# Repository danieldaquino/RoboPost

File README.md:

## An autonomous delivery system — By Daniel D'Aquino and Tim Yue

The aim of this project is to build a line following robot that will follow a line at a constant speed and be able to recognize different docking zones scattered around the track and park there.

**Note:** This project is retired and not under current development. Feel free to contact us if needed.

# SHOW ME THE DEMO!!

Here you go: [RoboPost Demo Video – Youtube](https://www.youtube.com/watch?v=mAnifTH91ZA)

# How does it work?

If you want to know how it works in more details, please visit our wiki!

[How it works — Wiki](https://github.com/danielwalnut/RoboPost/wiki)

# Setting up your own RoboPost

## Getting the hardware

Our custom hardware was designed and built with 3d printed parts, and our own lab-etched PCB boards.
We also made the assembly in a lab.

If you are interested in building your own custom robot based on our design, read on.

### Components needed

1. MSP4305529LP Evaluation Board
2. Particle Photon
3. TI DRV8871 Adafruit Breakout Board
4. 2 6V DC Motors with attached encoder
5. SparkFun Line Follower Sensor Array
6. Grove I2C Color Sensor Module
7. 3d-printed Chassis *(Custom-built)*
8. 3d-printed Motor couple *(Custom-built)*
9. PCB Main Dedicated Board *(Custom-built)*
10. Two wheels
11. Omni-wheel
12. 2 Cell (7.4V) Lipo battery
13. 5V Voltage regulator
14. 3v3 Voltage Regulator
15. Battery Voltage monitor
16. Track *(Custom-built)*
17. Docking Stations *(Custom-built)*

### Schematic

The schematic below is from the PCB Main dedicated board design. It does not include some connections external to the board.

Connections external to the board are done by connecting external pins. This includes:

1. From battery to Battery terminal
2. From motor driver output to motor
3. From power pins (3v3/5v) to sensor power inputs
4. From i2c pins in sensors to i2c bus on the board.

### Installing Software into your computer

Now that you have the hardware, it is time to setup the software!

**Note:** This installation procedure assumes you have a UNIX operating system, such as macOS or Linux, and that you are familiar with the command line. If you are using Microsoft Windows, some steps might be different.
**Note:** This installation procesure also assumes that the RoboPost firmware for both MSP430 and Particle Photon are already flashed into the robot.

1. Remove the robot from packaging.
2. Attach the battery to the velcro tape mount.
3. Connect Voltage Monitor. A loud beep will occur and the voltages should appear on screen.
4. You should see 6.7V minimum on the total voltage monitor. If it is below, it is necessary to charge the battery, or the robot will not work as expected
5. Connect the battery terminals to the Robot.
6. You should immediately see the Line Follower Array and the Photon light up.
7. Setup the Photon to connect to the Wi-Fi network of your choice. *More instructions on that can be found on [https://setup.particle.io](https://setup.particle.io)*
8. Make sure you have Git [https://git-scm.com/](https://git-scm.com/)
9. Clone this repo into your computer
	```$ git clone https://github.com/danielwalnut/RoboPost.git```
10. Generate a keys.json file within the Web folder. This allows the Node.js Application to connect to the correct device.
	```
	$ cd RoboPost/Web
	$ touch keys.json
	```
	Then open the file, and create its contents, **in the following format:**
	```
	{
	    "ID": <YOUR PARTICLE-ACCOUNT-ID IN DOUBLE QUOTES>,
	    "Token": <YOUR PHOTON-ACCESS-KEY IN DOUBLE QUOTES>
	}
	```
	Your keys can be found at [https://console.particle.io](https://console.particle.io)
11. Make sure you have Node.js 8.x.x [https://nodejs.org/en/](https://nodejs.org/en/) and NPM [https://npmjs.com/](https://npmjs.com/)
12. In order to install the required module packages, open a UNIX terminal, make sure you are in the ```Web``` folder and type:
	```$ npm install```
13. Now the installation should have been successful. Make sure the installation happened with no error
14. The software is now setup.

### Operating the Robot

1. After the robot is assembled and software is installed, power the robot by plugging the battery connector with power on the board.
2. Make sure Photon is connected to the same Wi-Fi network as the computer.
3. On a UNIX terminal, go to the ```Web``` folder and start the server:
	```
	$ cd <path-to-RoboPost>/Web
	$ npm start
	```
4. After a few seconds, you should see on the screen

5. Open your favorite web browser and go to [http://localhost:3000/](http://localhost:3000/)
6. The user interface will be displayed, to adjust parameters, click the cog at top right corner and drag the sliders. To set the robot in motion, click the **play** button on top left corner of the *UI* then press **PB1** on the *MSP430*.
7. To download statistic information, click the **download** button to the left of the cog in the *UI*.

# Hacking RoboPost

If you want to improve the software in RoboPost to suit your needs, you will need to understand the firmware more deeply.

General information about each module can be found in the ```README.md``` of most modules, and deeper information, such as descriptions of each functions can be found in the header ```.h``` files of most modules.

# Questions?

Feel free to open an issue

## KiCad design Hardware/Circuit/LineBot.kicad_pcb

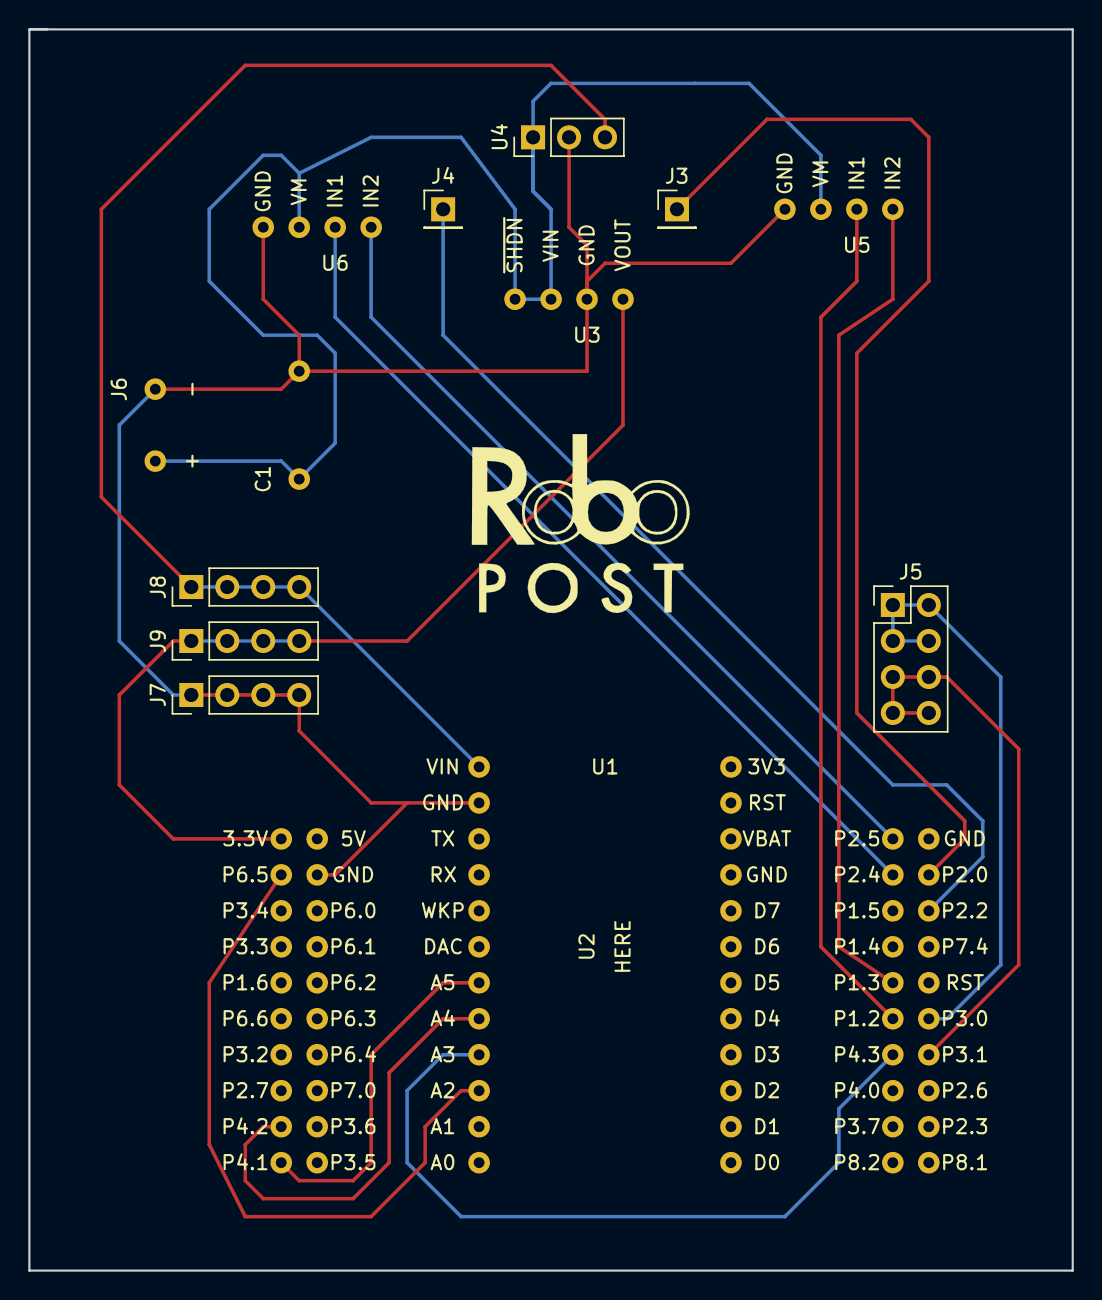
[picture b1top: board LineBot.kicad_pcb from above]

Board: 2 copper layers, 73.7 x 87.6 mm, 14 parts (0 on the bottom side), 16 nets.

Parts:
C1: 0.1u; CAP
J3: LEFT ENCODER; Pin_Header_Straight_1x01_Pitch2.54mm
J4: RIGHT ENCODER; Pin_Header_Straight_1x01_Pitch2.54mm
J5: I2C BUS; Pin_Header_Straight_2x04_Pitch2.54mm
J6: BATTERY TERMINAL; BATTERYBLOCK
J7: GND; Pin_Header_Straight_1x04_Pitch2.54mm
J8: 5V POWER; Pin_Header_Straight_1x04_Pitch2.54mm
J9: 3.3V POWER; Pin_Header_Straight_1x04_Pitch2.54mm
U1: MSP430
U2: Photon
U3: D24V6F3
U4: L7805; Pin_Header_Straight_1x03_Pitch2.54mm
U5, U6: DRV8871

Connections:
/LEFT_MOTOR_FORWARD: U1.36, U5.2
/LEFT_MOTOR_REVERSE: U1.35, U5.1
/MISO: U1.9, U2.8
/MOSI: U1.10, U2.7
/RIGHT_MOTOR_FORWARD: U1.32, U6.2
/RIGHT_MOTOR_REVERSE: U1.31, U6.1
/SCL: J5.5, J5.6, J5.7, J5.8, U1.27
/SCLK: U1.37, U2.9
/SDA: J5.1, J5.2, J5.3, J5.4, U1.26
/~SS: U1.2, U2.10
GND: C1.2, J6.2, J7.1, J7.2, J7.3, J7.4, U1.12, U2.2, U3.2, U4.2, U5.4, U6.4
unnamed: C1.1, J6.1, U3.3, U3.4, U4.1, U5.3, U6.3
unnamed: J3.1, U1.22
unnamed: J4.1, U1.23
unnamed: J8.1, J8.2, J8.3, J8.4, U2.1, U4.3
unnamed: J9.1, J9.2, J9.3, J9.4, U1.1, U3.1

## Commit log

2018-01-12 README.md
2018-01-12 Fixed typo
2018-01-12 Added my name to README
2018-03-02 Added Tim to license
2018-03-02 Forked TI pwmled with TIRTOS example as a starting point. Also added the GCC build folder, changed the makefile and kept Windows CCS config files
2018-03-03 added some comments
2018-03-03 Added the hidden files
2018-03-03 Excluded GCCBuild from ccs build configs, and on ccs I added the TI_RTOS_GCC project.
2018-03-03 Changed maximum pwm duty cycle to 88%, but it goes to 90% (measured)
2018-03-03 Added UART Terminal
2018-03-03 Added automatic building bash script for the gcc toolchain, and coded an interrupt counter with a button
2018-03-09 NO MORE CC3220. Switching to MSP430 + Particle Photon
2018-03-09 Added MSPMotorControl
2018-03-10 Removed old CCS hidden files and added new CCS hidden files
2018-03-10 robopo updated
2018-03-10 Removed the CCS files
2018-03-10 Removed debug files from git scope
2018-03-10 deleted the stoopid file
2018-03-11 Added used resources to README
2018-03-11 Beautified README
2018-03-11 Added Logo
2018-03-11 Added more specified things on readme
2018-03-11 Implemented Dual Motor driving, and implemented reverse PWM signal
2018-03-11 Added small test for 2 motor driving. Motor works. Logging is screwed up.
2018-03-11 Fixed hard coded limit where there was supposed to be a MACRO.
2018-03-11 Fixed multiple bugs preventing the two Motor control from working
2018-03-11 Added the dual motor controller as a module. I still need to set automatic Feedback updates
2018-03-13 Added partial schematics
2018-03-13 Changed header style
2018-03-13 Added Scheduler to handle all updating functions
2018-03-13 Changed main. No need to keep changing setpoint... yet.
2018-03-13 implemented i2c but still have problem with defines
2018-03-13 Fixed define error. What happened was that variable values were being defined twice, if code was included twice. variables are not suppose to be defined on the header file, only declared.
2018-03-13 Added an integrator and a saturator, and eliminated almost completely the steady state error
2018-03-13 Fixed wiring mistake, disabled the negative duty cycle for now
2018-03-14 Fixed wrong declaration
2018-03-14 Fixed outdated headers
2018-03-14 Implemented differential drive
2018-03-14 commented on I2C_modual.h file
2018-03-14 Updated motor driver and all dependencies to allow for independent Frequency Modulation besides PWM. Now this is a FPWM motor driver
2018-03-14 Completed a working 3 gear frequency modulation. I was able to go to 90 RPM with +/- 3RPM offset and motor 2 went to 250RPM with low offset
2018-03-14 Added possibility of setting negative curve radius
2018-03-14 seperated one module to two: LineSensorDriver and I2C_modual
2018-03-15 Increased UARTIO buffer size and fixed bug that would cause memory conflicts
2018-03-15 Changed method of forced synchronous mode from CPU_OFF to flag polling, for enhanced debugging.
2018-03-15 Changed the UARTIOSend to fix a possible stack corruption
2018-03-15 Styled the code, put things in their right module, structured more
2018-03-15 Updated used resources
2018-03-15 Updated list of components
2018-03-15 Added a PD controller to the motor controller, and reduced Kp to add damping and reduce overshoot.
2018-03-15 Fixed the spec on the line following sensor to float from -1 to 0 to 1
2018-03-15 Moved files to accomodate new software structure, and designed draft for the line cruiser. THIS IS UNTESTED
2018-03-15 Added an empty file to show the Photon folder
2018-03-16 Added some basic files to get started
2018-03-16 Fixed multiple bugs with the line cruiser
2018-03-23 Fixed some bugs, and added heartbeat
2018-03-24 Added start stop module
2018-03-24 Added start stop functionality, disabled UART, and made setpoint slower
2018-03-24 Made max values saturate, and made changes to linecruiser algorithm
2018-03-24 Fixed a deadly min curvature radius bug
2018-03-25 Exposed setpoints in diffdriver to outside module, Improved Start Stop logic, Exposed diffDriver setpoints to UART IO, Made robot normally stopped for safety
2018-03-25 Fixed direction of KD
2018-03-25 Optimization phase 1, Test 2
2018-03-25 Optimization phase 1, Test 3
2018-03-25 Optimization phase 1, test 4
2018-03-25 Opmization phase 1, test 5
2018-03-25 Optimization phase 1, test 6
2018-03-25 Optimization phase 1, test 7
2018-03-25 Optimization phase 1, test 8
2018-03-25 Optimization phase 1, test 9
2018-03-25 Optimization phase 1, test 10
2018-03-25 Optimization phase 1, test 11
2018-03-25 Optimization phase 1, test 12
2018-03-27 Got to the point where I am able to call a request in JS programmatically, receive response from node.js server
2018-03-27 Deleted node module files which will be ignored
2018-03-27 npm added a package-lock file
2018-03-27 Made the GET request to local server turn on and off photon's D7 LED
2018-03-27 Made web interface that turns on or off an LED
2018-03-27 Perfected the system variables, back to test 9, and made the sensor read faster.
2018-03-28 Optimization phase 1, test 13
2018-03-28 Made basic layout
2018-03-28 Added canvas, autoresize, and renders the car and the curvature radius
2018-03-28 Enabled negative curve radius
2018-03-28 Made many changes to the block drawing, and added relative positioning, and PWM diagram
2018-03-28 Finished first full version of the motor box
2018-03-29 Created better start stop button
2018-03-29 Added Settings Panel
2018-03-30 Made improvements to the settings panel UI
2018-03-30 Added the speed box.
2018-03-30 Made server backend get photon's local IP address, and made a kickass welcome banner
2018-04-01 Implemented a working TCP interface between Photon and Node.js backend
2018-04-01 Made lots of measurements update in realtime
2018-04-01 Implemented download feature
2018-04-02 addition of new module:SPI WITH PHOTON
2018-04-02 some changes were not saved now it is
2018-04-02 Made the Measurements be transmitted in one way transmittion event with no lossless protection, for performance. Also, changed measurements stream protocol to websockets between node and web
2018-04-02 Made a huge leap in structure for web interface
2018-04-02 Made changes to follow the established communication protocol.
2018-04-02 Fixed some settings panel bugs
2018-04-02 Successfully sent the encoded parameters to the photon
2018-04-02 Moved Photon code to Photon folder
2018-04-02 Moved ucsiSpi module to its own folder, fixed some indentation issues and created blank header file
2018-04-02 Fixed indentation issues
2018-04-02 Renamed module files
2018-04-02 Readded previously deleted code to main
2018-04-03 Styled and documented this branch
2018-04-03 Integrated with existing code and made simple test
2018-04-03 Made changes to make it compile with photon
2018-04-03 Got one way MSP-SPI-PHOTON-TCP-NODE-WEBSOCKETS-WEB of data stream working
2018-04-03 Completed full data loop between MSP and web interface
2018-04-04 Fusion of MSP-Web loop with Robot control successful
2018-04-05 Implemented clutch
2018-04-06 put bitscounted in global var
2018-04-06 added one more element to the array and also moddified photon code to accomondate the change
2018-04-06 Updated web interface to accept speed control
2018-04-06 Fixed UI issues
2018-04-12 Made the speed actually update on the feedback system
2018-04-12 Now the CSV will only record when playing, to avoid painfully long and useless spreadsheets
2018-04-13 Made UI settings all visible
2018-04-13 Now the timestamp will be the uptime in milliseconds
2018-04-13 Fixed CSV organization issues and now it only records on play, avoiding awful long spreadsheets
2018-04-13 Changed timestamp format to match millis function, preventing short term overflow issues
2018-04-13 Updated UI to provide default settings, and now it always shows beginning values, and initial values are always sent to the photon on start
2018-04-13 Can communicate through I2C and recognize blue and red
2018-04-14 connected two color and line sensor on the bus and it worked. then optimized code
2018-04-14 fixed spelling error
2018-04-14 Implemented new scheduler
2018-04-14 Improved UI, fixed bugs
2018-04-15 Increased PWM resolution
2018-04-16 Added CRC checksum, and fixed glitch
2018-04-24 Added integrator and the decay recover
2018-04-24 Added Ki and decay rate to infoboard
2018-04-24 Updated visual feedback
2018-04-24 Made it decay to absolute speed
2018-04-24 First draft files
2018-04-27 Fixed bug in PBrake
2018-04-27 Implemented fork driving
2018-04-27 Added a system that can save parameters
2018-04-28 changed font to quicksand
2018-04-28 Changed the limit on the cruise kd
2018-04-29 Implemented Dynamic Braking
2018-04-29 Added Hardware to .gitignore temporarily
2018-04-29 Revert "Implemented Dynamic Braking"
    This reverts commit b969c98568609f0ee620f5e846148c1e2f46f854.
    Reverted dynamic braking
2018-04-29 del main
2018-04-29 integration in progress
2018-04-30 Implemented the color on on the web interface
2018-04-30 implemented color switching instead of stop for 3 sec
2018-04-30 Fixed many bugs
2018-05-02 Fixed UI bugs
2018-05-02 Added RGB color to infoboard
2018-05-03 Added Free run feature
2018-05-03 curve radius is float
2018-05-03 Added measurements setting to 30Hz
2018-05-04 Put a delay into the Docking feature, to avoid burst errors that eventually bypass the CRC
2018-05-04 Added new state logic to GUI that allows to go to the next station of same color
2018-05-04 Tried to make a new integrator type
2018-05-04 Implemented an activation function
2018-05-04 Added an integrator
2018-05-04 Fixed some bugs on the feature
2018-05-04 Fixed bug with dynamic breaking
2018-05-07 Added draft for fork line recovery mode
2018-05-08 Fixed some bugs with fork recovery mode
2018-05-08 Fixed bug that would make it go crazy after converging fork
2018-05-08 Added basic map
2018-05-08 Drag and drop logic complete
2018-05-08 Made working drag/drop UI with the underlying model updating
2018-05-08 Added path chosen to the info board
2018-05-09 Made map look nicer
2018-05-09 Changed threshold values to avoid errors
2018-05-09 Added fast start stop
2018-07-27 Changed sensibility back
2018-07-27 Deleted some hardware files
2018-07-28 Changed README.md drastically
2018-07-28 Added my email
2018-07-28 Tweaks to readme
2018-07-28 more Tweaks to readme
2018-07-28 Added readme to the LineCruiser
2018-07-28 Added all the line sensor driver docs
2018-07-28 Added correct picture
2018-07-28 Fixed formatting issue
2018-07-28 Deleted picture
2018-07-28 readded pictures
2018-07-28 removed step 5 img
2018-07-28 Readded picture
2018-07-28 deleted step5 pic
2018-07-28 Readded picture of step 5
2018-07-28 deleted step2
2018-07-28 deleted step5
2018-07-28 Added new pictures which hopefully won't be with a gradient
2018-07-28 Fixed names
2018-07-28 Added motion planning documentation
2018-07-28 Added Motion execution
2018-07-28 Added docs about the Interface with the Web
2018-07-28 Added docking docs
2018-07-28 Fixed codeblock formatting
2018-07-28 Added link to wiki
2018-07-28 Fixed broken link
2018-07-28 Added more emphasis to the demo video
